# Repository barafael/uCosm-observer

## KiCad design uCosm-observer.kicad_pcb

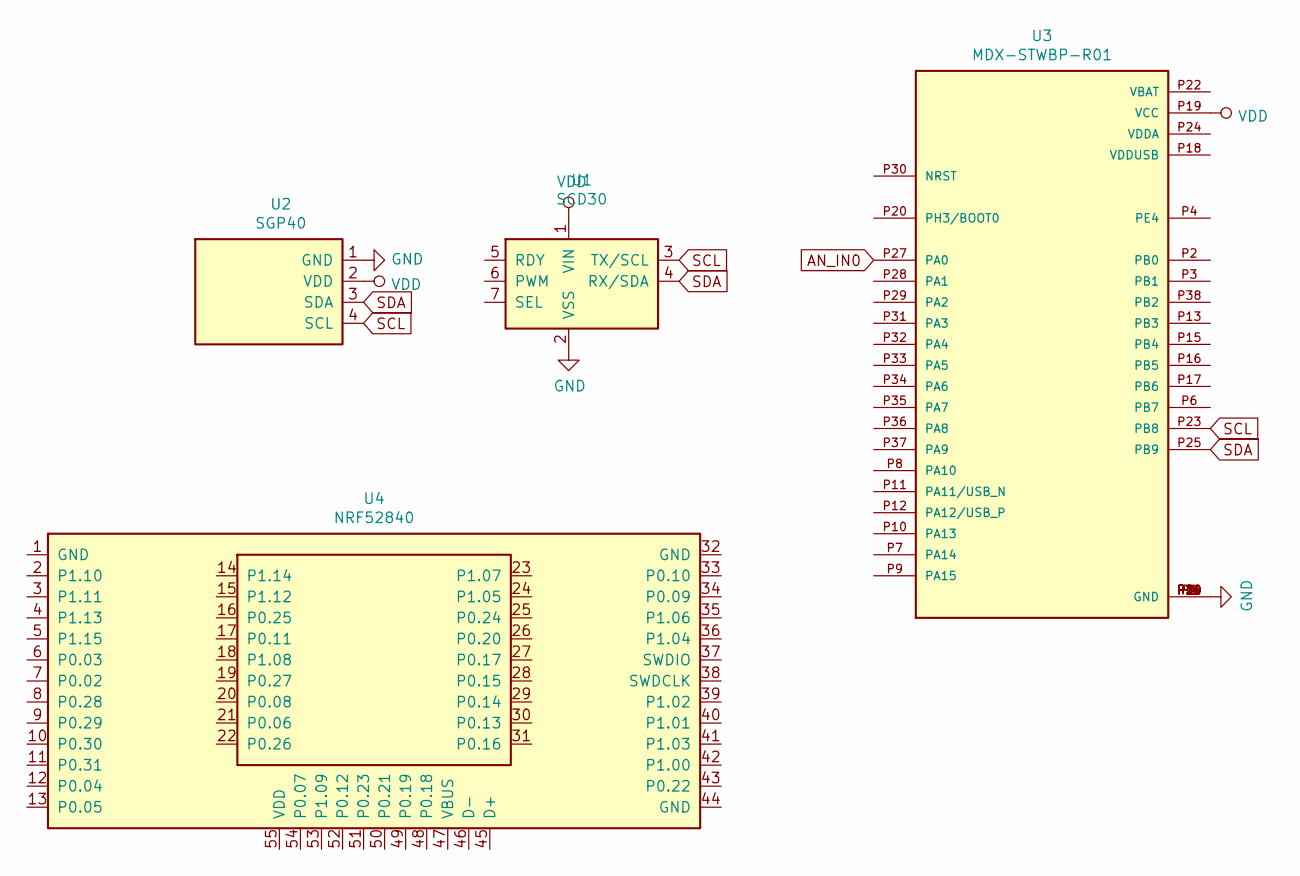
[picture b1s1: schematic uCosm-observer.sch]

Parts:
U1: SCD30; scd30
U2: SGP40; sgp40-sparkx-breakout
U3: MDX-STWBP-R01; XCVR_MDX-STWBP-R01; PARTREV 1.5
U4: NRF52840; nrf52-waveshare

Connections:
AN_IN0: U3.P27 (PA0)
GND: U1.2 (VSS), U2.1 (GND), U3.P1 (GND), U3.P5 (GND), U3.P14 (GND), U3.P21 (GND), U3.P26 (GND), U3.P39 (GND), U3.P40 (GND)
SCL: U1.3 (TX/SCL), U2.4 (SCL), U3.P23 (PB8)
SDA: U1.4 (RX/SDA), U2.3 (SDA), U3.P25 (PB9)
VDD: U1.1 (VIN), U2.2 (VDD), U3.P19 (VCC)

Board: 2 copper layers, 4 parts (0 on the bottom side), 4 nets, no tracks yet.

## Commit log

2021-06-13 Add scd30 + sgp40 schematic submodules
2021-06-13 Add scd30 + sgp40 footprints
2021-06-13 Add MDX WB55 module
2021-06-16 Add nrf52 waveshare board to compare with stm32wb55
